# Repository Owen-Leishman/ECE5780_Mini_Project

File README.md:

# Demonstration Neural Interface
>[!warning]
>This is a demonstration device, this hardware is relatively untested and not gauranteed to be safe! This is not designed live test subjects!

## Overview
This is a demonstration neural interface which is meant to explore how neural interfaces work.  This device can measure four differential signals at a time which can be used to measure nerve impulses and are tolerant of ±9V. It also has a current mode stimulation channel which can create ±1mA signals with 9 bits of resolution as a means to give feedback to the nerves. The stimulation channel can handle electrodes with up to 9kΩ. The device also has a temperature sensor to measure how much it heats up to ensure that it would be safe if implanted (at least temperature wise). The device can be controlled over wifi, and is fully battery powered.

(A logo was edited out on the bottom left corner of the device, the photo is otherwise not edited)

## Organization
- [Firmware](/Firmware/Neural_Demo/) contains the code that the device runs.
- [Hardware](/Hardware/) contains the design of the device.
- [Software](/Software/) contains the code used to interface with the device.

For information on how to use the device refer to the [software directory](/Software/).

For information on how to manufacture the device refer to the [hardware directory](/Hardware/).

## Results
The device has exceptional accuracy and can measure down to the uV using its discreate ADC.

This test was run using an external signal generator to create a 1mV peak-to-peak sine wave at 500mHz. (This test was also done with old software and firmware some of the ADC configuration has been changed).

The demonstration software makes it possible to measure all four channels in real time over wifi, and the measured stimulation current. The software also makes it possible to control the amplitude and waveform the current stimulation uses.

The discreate ADC broke so the ESP32's onboard ADC (which is much worse) was used for this test. An external signal generator was connected to channel 1 to create a 1V peak-to-peak sine wave, and an external load resistor was used to connect the stimulation output to ground.

# Design Overview
Here are is the top level design of the device, for detailed information on the desing refer to the [hardware directory](Hardware).

## Top Level Design

The ESP32 microcontroller is used to control the whole device. The analog frontend is used to aquire data from the differential inputs, and output stimulation signals. The power distrobution block manages the battery and all of the supply voltages.

## Analog Frontend

## Power Distrobution

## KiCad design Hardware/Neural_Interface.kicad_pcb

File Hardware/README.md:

# Demonstration Neural Interface Hardware
>[!warning]
>This is a demonstration device, this hardware is relatively untested and not gauranteed to be safe! This is not designed live test subjects!

>[!note]
>Made with KiCad version 7.0,  [Kicad Download](https://www.kicad.org/download/)

The hardware for the demonstration neural interface.

## Tasks
- [ ] Test BQ51013BRHLR wirless power IC.
- [ ] Add voltage divider/modify signal path for onboard ADC.
- [ ] Find replacement for AD8067ARTZ operational amplifier used in the current source.
- [ ] Find issues with MCP3464 ADC (may have been ESD)

# Assembled Device

>[!warning]
>This device uses BGA components and is not trivial to solder. Due to the large amount of surface mount components on the device it is recomended to use a stencil and a reflow oven for soldering.

## Current Source Fix

The AD8067ARTZ was broken (reason still unknown) so a LF353N was used to replace it for testing.

## Onboard ADC Fix

The MCP3464RT ADC broke so the ESP32's onboard ADC was used. The onboard ADC can not measure voltages larger than ~200mV so voltage dividers were added to divide all of the signals into that range, 4.7K and 180R resistors were used to create the voltage dividers. This creates a lot of noise and distortion in the signals. Due to this onboard ADC will not be used or supported in future revisions.

# Schematics
## Top Level Schematic

Schematic for the ESP32 S2-mini and supporting circuitry which is used to control the device. Jumpers are added between the ESP32's gpio and board signals to make it possible to rerout signals if there is a conflict, or prevent interference for analog signals if the onboard ADC is not being used. The temperature sensor is also on this schematic.

## Analog Frontend Schematic

Schematic for the analog frontend used to measure "neural" signals and output current mode stimulation. The differential input signals are fed into voltage dividers to ensure that the maximum voltage that reaches the system is ±3.3V, and to create a 1MΩ input impedance. Instrumentation amplifiers are used to amplify the differential signals (satureates at ±1V but is tolerant fo ±9V) and convert them to single ended signals (0-3.3V) centered around Vref (1.6V). The outut of the instrumentation amplifiers is fed into a buffered opamp with a shotkey diode to prevent negative voltages from reaching the ADC when the instrumentation amplifiers get saturated with a negative signal (Ie. an input of -9V), this opamp will likely be removed in future revisions. Low pass filterers and decoupling capacitors are implemented throughout the design to reduce noise.

The current mode stimulation is created using an advanced howland current source implementation based on an [article by Nick Jiang from Analog Devices](https://www.analog.com/en/resources/analog-dialogue/articles/a-large-current-source-with-high-accuracy-and-fast-settling.html). The current sources is controlled by using both DACs on the ESP32, one DAC is used for creating positive currents while the other is used to create negative curents. The maximum output current is ±1mA when 3.3V is supplied by one of the DACs. The maximum probe impedance the current source can handle is 9kΩ, since the stimulation voltage is ±9V. A capacitor is added in series to the output current to prevent continous stimulation in case of a device malfunction (this capacitor was shorted to test the current source at low frequencies).

## Power Manegement Schematic

Schematic for the power manegement circuitry which supplies power to the device and maneges the battery. The device can be powered from using wireless charging, USB type C, or the onboard battery. The BQ51013BRHLR wireless charging IC automatically selects if the BQ25185DLHR battery charging IC will be suplied with usb power or wireless power based on which one is present. The battery charging IC controlls the battery charge rate, and charge and discharge threshold and determines if the voltage regulators for the rest of the system will be supplied with battery power or the power selected by the wireless charging IC. A BQ27427YZFR is placed in series with the battery to measure battery life.

There are three voltage regulators on the device. A buck converter supplies Vsys (+3.3V) to power the ESP32 and TMP117, it is always on when voltage is present. A differential boost converter suplies Vstim (±9V) which poweres the constant current source and is controlled by the ESP32. The rest of the analog frontend is powered with a differential linear dropout regulator (LDO) which is powered from Vstim and reduces the supply noise caused by the switching regulators creating ±3.3V, this is not very effecient and will likely be changed in future revisions. The LDO is always on whenever Vstim is present.

# PCB Layout

>[!note]
>These figures are for reference, there may be some visual issues due to how KiCad exports SVG files.

## Top PCB Layout

## Bottom PCB Layout

## 3D Render

# Ordering
The design is layed out as a two layer board following [JLC PCB's](https://jlcpcb.com/) constraints, and all components are placed on the top layer. To order zip the [NSD_V1-0](Hardware/NSD_V1-0) directory and submit it to JLC PCB. A stencil can also be ordered from JLC PCB.

All of the parts other than the battery and battery connector can be ordered from [Mouser Electronics](https://www.mouser.com/) and listed [here](Hardware/MouserPartsOrder.xls). The battery and battery connector can be ordered from [DigiKey](https://www.digikey.com/) and are listed [here](Hardware/DigiKeyPartsOrder.xlsx). The [BOM](Hardware/BOM.csv) does not reference passive parts with manufacturer names. Additionaly 2.54mm headers are not included in either of these lists.

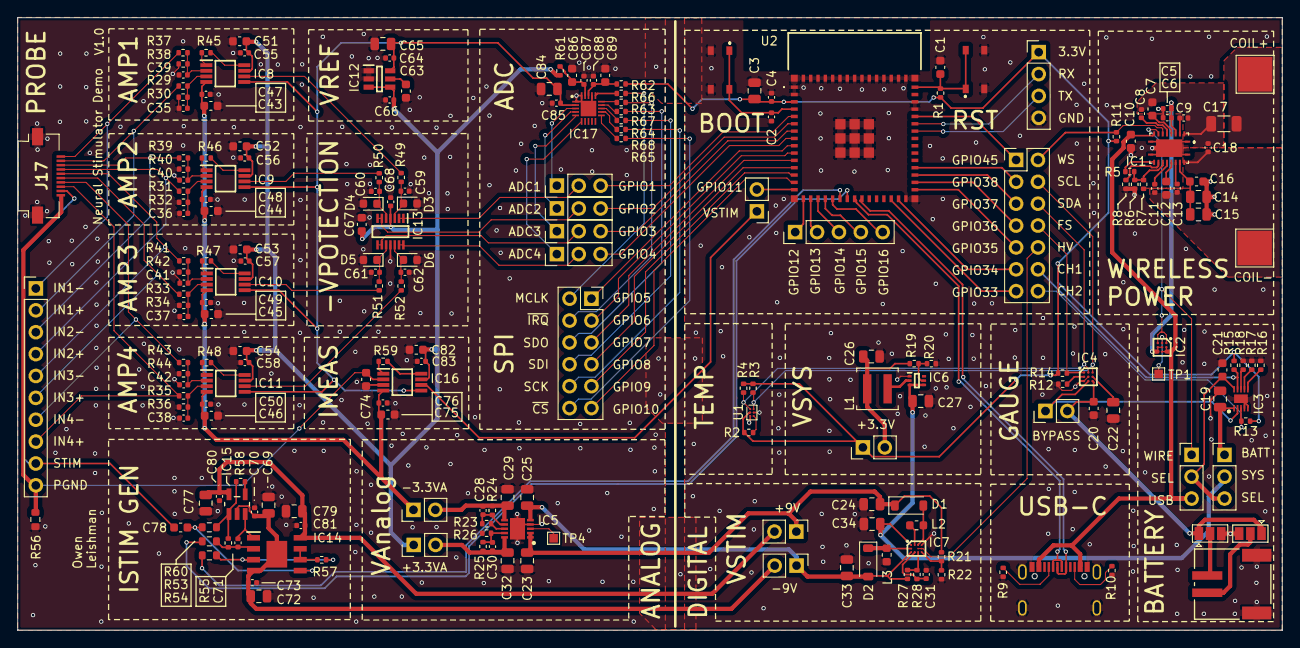
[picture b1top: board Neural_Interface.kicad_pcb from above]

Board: 2 copper layers, 146.9 x 71.1 mm, 214 parts (0 on the bottom side), 161 nets.

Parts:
C1, C10, C16, C20, C21, C43, C44, C45, C46, C51, C52, C53, C54, C63, C67, C74, C75, C78, C82, C86, C89: 1u; C_0603_1608Metric
C2, C4, C5, C31, C47, C48, C49, C50, C55, C56, C57, C58, C64, C66, C68, C70, C73, C76, C80, C81, C83, C85, C87, C88: 100n; C_0402_1005Metric
C3, C14, C15, C19, C22, C23, C24, C25, C26, C27, C29, C32, C33, C34, C65, C69, C72, C77, C79, C84: 10u; C_0805_2012Metric
C6, C9, C13, C28, C30: 10n; C_0402_1005Metric
C7, C12: 470n; C_0603_1608Metric
C8, C11: 47n; C_0402_1005Metric
C17: 82n; C_1206_3216Metric
C18: 820p; C_0402_1005Metric
C35, C36, C37, C38, C39, C40, C41, C42, C59, C60, C61, C62: 30p; C_0402_1005Metric
C71: 200p; C_0402_1005Metric
D1, D2: MBR130T1G; D_SOD-123
D3, D4, D5, D6: CDBU0130L-HF; D_0603_1608Metric
IC1: BQ51013BRHLR; BQ51050BRHLR
IC2: CSD75207W15; BGA9C50P3X3_146X146X62
IC3: BQ25185DLHR; SON40P220X200X80-11N
IC4: BQ27427YZFR; BGA9C50P3X3_158X162X62
IC5: TPS7A3901DSCR; SON50P300X300X80-11N-D
IC6: TLV62585DRLR; SOTFL50P160X60-6N
IC7: BD8316GWL-E2; BGA11C40P4X3_180X150X55
IC8, IC9, IC10, IC11, IC16: INA823DGKR; SOP65P490X110-8N
IC12: REF35160QDBVR; SOT95P280X145-6N
IC13: LM324LVIDYYR; SOP50P326X110-14N
IC14: ADA4898-2YRDZ; SOIC127P600X175-9N
IC15: AD8067ARTZ-REEL7; SOT95P280X145-5N
IC17: MCP3464RT-E_NC; QFN40P300X300X60-21N-D
J1: Conn_02x07_Odd_Even; PinHeader_2x07_P2.54mm_Vertical
J2: Conn_02x06_Odd_Even; PinSocket_2x06_P2.54mm_Vertical
J3: Conn_01x05; PinHeader_1x05_P2.54mm_Vertical
J4: Conn_01x04; PinHeader_1x04_P2.54mm_Vertical
J5, J10, J18, J19, J20, J21: Conn_01x03; PinHeader_1x03_P2.54mm_Vertical
J6, J11, J12, J13, J14, J15, J22: Conn_01x02; PinHeader_1x02_P2.54mm_Vertical
J7: S2B-PH-SM4-TB; CONN_S2B-PH-SM4-TB_JST
J8, J9: Conn_01x03; SolderJumper-3_P1.3mm_Open_Pad1.0x1.5mm
J16: Conn_01x10; PinHeader_1x10_P2.54mm_Vertical
J17: 505110-1092; 5051101092
L1: 1uH; L_Coilcraft_XAL4020-XXX
L2, L3: 4.7uH; L_0603_1608Metric
R1, R2, R3, R4, R8, R11, R12, R13, R14, R15, R16, R22, R23, R26, R28, R49, R50, R51, R52: 10k; R_0402_1005Metric
R5: 330; R_0402_1005Metric
R6: 196; R_0402_1005Metric
R7: 20k; R_0402_1005Metric
R9, R10: 5.1k; R_0402_1005Metric
R17: 130k; R_0402_1005Metric
R18: 3k; R_0402_1005Metric
R19: 453k; R_0402_1005Metric
R20, R21: 100k; R_0402_1005Metric
R24: 28k; R_0402_1005Metric
R25: 17.8k; R_0402_1005Metric
R27: 90.9k; R_0402_1005Metric
R29, R31, R33, R35, R37, R39, R41, R43: 600k; R_0402_1005Metric
R30, R32, R34, R36, R38, R40, R42, R44: 332k; R_0402_1005Metric
R45, R46, R47, R48: 24.9k; R_0402_1005Metric
R53, R54: 82.5k; R_0603_1608Metric
R55, R57: 100R; R_0402_1005Metric
R56: 1R; R_0603_1608Metric
R58: 2k; R_0402_1005Metric
R59: 200; R_0402_1005Metric
R60: 4R; R_0603_1608Metric
R61, R62, R63, R64, R65, R66, R67, R68: 10R; R_0402_1005Metric
SW1: RESET; PTS815SJM250SMTRLFS
SW2: BOOT; PTS815SJM250SMTRLFS
TP1, TP4: TestPoint; TestPoint_Pad_1.0x1.0mm
TP2, TP3: TestPoint; TestPoint_Pad_4.0x4.0mm
U1: TMP117; Texas_DSBGA-6_0.95x1.488mm_Layout2x3_P0.4mm
U2: ESP32S2MINI1N4R2
U3: USB4105

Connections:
5v_Batt: C19.1, IC3.1 (SYS), J10.1
5v_Sel: C21.1, IC3.10 (IN), J5.2, J10.3
5v_Sys: C27.1, C34.1, IC6.3 (VIN), IC6.4 (EN), IC7.A1 (VDD), J10.2
5v_USB: C10.1, IC1.9 (AD), IC2.A2 (D1_1), IC2.A3 (D1_2), IC2.B3 (D1_3), J5.3, U3.2 (A4-B9), U3.11 (B4-A9)
5v_Wireless: C5.1, C6.1, IC1.4 (OUT), IC2.B2 (D2_1), IC2.C2 (D2_2), IC2.C3 (D2_3)
+3.3V: C3.1, C4.1, J4.1, J13.1, R1.1, R2.2, R3.2, R4.2, R11.1, R13.1, R14.1, R15.1, R62.2, U1.B1 (V+), U2.3 (3V3)
+3.3VA: C51.1, C52.1, C53.1, C54.1, C55.1, C56.1, C57.1, C58.1, C66.1, C67.1, C68.1, C82.1, C83.1, IC8.7 (+VS), IC9.7 (+VS), IC10.7 (+VS), IC11.7 (+VS), IC12.3 (EN), IC12.4 (VIN), IC13.4 (V+), IC16.7 (+VS), J14.1, R61.2
+3.3va: C30.1, C32.1, IC5.10 (OUTP), J14.2, R25.1
+3v: C26.1, J13.2, L1.1, R19.1
+9v: C23.1, C24.1, D1.1 (K), IC5.1 (INP), IC5.2 (EN), J11.1, R21.1
-3.3va: C28.2, C29.1, IC5.6 (OUTN), J15.2, R24.2
-3V3: C43.1, C44.1, C45.1, C46.1, C47.1, C48.1, C49.1, C50.1, C75.1, C76.1, IC8.4 (-VS), IC9.4 (-VS), IC10.4 (-VS), IC11.4 (-VS), IC16.4 (-VS), J15.1
-9v: C25.1, C33.1, D2.2 (A), IC5.5 (INN), IC7.C1 (DIS1), J12.1, R27.1
AC1: C7.1, C8.1, C9.2, C17.2, C18.1, IC1.2 (AC1)
AC2: C11.1, C12.1, C13.2, C18.2, IC1.19 (AC2), TP3.1
ADC_1: J19.3, U2.5 (IO1)
ADC_2: J18.3, U2.6 (IO2)
ADC_3: J20.3, U2.7 (IO3)
ADC_4: J21.3, U2.8 (IO4)
ADC_5: J22.2, U2.15 (IO11)
ALERT: R2.1, U1.C2 (ALERT)
BOOT: C2.2, SW2.1, U2.4 (IO0)
Batt+: J7.1, J8.2
Batt-: J7.2, J9.2
CHRG_STAT1: IC3.9 (STAT1), J1.12, R15.2
CHRG_STAT2: IC3.3 (STAT2), J1.14, R13.2
COIL+: C17.1, TP2.1
D+: U2.24 (IO20), U3.6 (A6), U3.8 (B6)
D-: U2.23 (IO19), U3.5 (B7), U3.7 (A7)
Fuel_Status: IC4.A1 (GPOUT), J1.8, R14.2
GND: C1.2, C2.1, C3.2, C4.2, C5.2, C6.2, C10.2, C14.2, C15.2, C16.2, C19.2, C20.2, C21.2, C22.2, C23.2, C24.2, C25.2, C26.2, C27.2, C29.2, C31.2, C32.2, C33.2, C34.2, C35.2, C36.2, C37.2, C38.2, C39.2, C40.2, C41.2, C42.2, C43.2, C44.2, C45.2, C46.2, C47.2, C48.2, C49.2, C50.2, C51.2, C52.2, C53.2, C54.2, C55.2, C56.2, C57.2, C58.2, C59.2, C60.2, C61.2, C62.2, C63.2, C64.2, C65.2, C66.2, C67.2, C68.2, C69.2, C70.2, C72.2, C73.2, C74.2, C75.2, C76.2, C77.2, C79.2, C80.2, C81.2, C82.2, C83.2, C84.2, C85.2, C86.2, C87.2, C88.2, C89.2, D3.2 (A), D4.2 (A), D5.2 (A), D6.2 (A), IC1.1 (PGND_1), IC1.10 (EN1), IC1.11 (EN2), IC1.20 (PGND_2), IC1.21 (EP), IC3.4 (~CE), IC3.5 (GND), IC3.11 (EP), IC4.B2 (VSS_1), IC4.C1 (VSS_2), IC5.4 (GND), IC5.11 (EP), IC6.1 (GND), IC7.A4 (GND), IC12.1 (GND_1), IC12.2 (GND_2), IC13.11 (V-), IC16.3 (+IN), IC17.1 (REFIN-), IC17.17 (DGND), IC17.20 (AGND), IC17.21 (EP), J4.4, J7.3 (SHIELD), J7.4 (SHIELD), J8.3, J9.3, J17.11, J17.12, L3.2, R6.2, R8.2, R9.1, R10.2, R12.2, R16.2, R17.2, R18.2, R20.2, R22.2, R26.2, R30.1, R32.1, R34.1, R36.1, R38.1, R40.1, R42.1, R44.1, R56.1, SW1.2, SW2.2, U1.B2 (GND), U1.C1 (ADD0), U2.1 (GND), U2.2 (GND), U2.30 (GND), U2.42 (GND), U2.43 (GND), U2.46 (GND), U2.47 (GND), U2.48 (GND), U2.49 (GND), U2.50 (GND), U2.51 (GND), U2.52 (GND), U2.53 (GND), U2.54 (GND), U2.55 (GND), U2.56 (GND), U2.57 (GND), U2.58 (GND), U2.59 (GND), U2.60 (GND), U2.61 (GND), U2.62 (GND), U2.63 (GND), U2.64 (GND), U2.65 (GND), U2.66, U2.67, U2.68, U2.69, U2.70, U2.71, U2.72, U2.73, U3.1 (A1-B12), U3.12 (B1-A12), U3.13 (GND)
GPIO5: J2.1, U2.9 (IO5)
GPIO6: J2.3, U2.10 (IO6)
GPIO7: J2.5, U2.11 (IO7)
GPIO8: J2.7, U2.12 (IO8)
GPIO9: J2.9, U2.13 (IO9)
GPIO10: J2.11, U2.14 (IO10)
GPIO12: J3.1, U2.16 (IO12)
GPIO13: J3.2, U2.17 (IO13)
GPIO14: J3.3, U2.18 (IO14)
GPIO15: J3.4, U2.19 (IO15)
GPIO16: J3.5, U2.20 (IO16)
GPIO33: J1.13, U2.28 (IO33)
GPIO34: J1.11, U2.29 (IO34)
GPIO35: J1.9, U2.31 (IO35)
GPIO36: J1.7, U2.32 (IO36)
GPIO37: J1.5, U2.33 (IO37)
GPIO38: J1.3, U2.34 (IO38)
GPIO45: J1.1, U2.41 (IO45)
HV_En: IC7.B3 (STB1), IC7.B4 (STB2), J1.10
Istim: IC16.6 (OUT), J22.1
MCLK: J2.2, R66.1
unnamed: D1.2 (A), IC7.A3 (LX2), L2.1
unnamed: D2.1 (K), IC7.B1 (LX1), L3.1
unnamed: C59.1, D3.1 (K), IC13.3 (IN1+), R49.1
unnamed: C60.1, D4.1 (K), IC13.5 (IN2+), R50.1
unnamed: C61.1, D5.1 (K), IC13.10 (IN3+), R51.1
unnamed: C62.1, D6.1 (K), IC13.12 (IN4+), R52.1
unnamed: C9.1, IC1.3 (BOOT1)
unnamed: C13.1, IC1.17 (BOOT2)
unnamed: C7.2, IC1.5 (CLAMP1)
unnamed: C12.2, IC1.16 (CLAMP2)
unnamed: C8.2, IC1.6 (COMM1)
unnamed: C11.2, IC1.15 (COMM2)
unnamed: IC1.14 (FOD), R5.2, R6.1, R7.1
unnamed: IC1.12 (ILIM), R5.1
unnamed: IC1.13 (TS/CTRL), R8.1
unnamed: IC2.B1 (SS), TP1.1
unnamed: IC3.7 (ILIM/VSET), R17.1
unnamed: IC3.8 (ISET), R18.1
unnamed: IC3.6 (TS/MR), R16.1
unnamed: IC4.B1 (BIN), R12.1
unnamed: C22.1, IC4.B3 (VDD)
unnamed: IC5.8 (BUF), R23.1
unnamed: C28.1, IC5.7 (FBN), R23.2, R24.1
unnamed: C30.2, IC5.9 (FBP), R25.2, R26.1
unnamed: IC5.3 (NR/SS), TP4.1
unnamed: IC6.5 (FB), R19.2, R20.1
unnamed: IC6.2 (SW), L1.2
unnamed: IC7.A2 (HS2L), L2.2
unnamed: IC7.C4 (INV2), R21.2, R22.1
unnamed: IC7.C3 (NON1), R27.2, R28.1
unnamed: C31.1, IC7.C2 (VREF), R28.2
unnamed: C35.1, IC8.3 (+IN), R29.1, R30.2
unnamed: C39.1, IC8.2 (-IN), R37.1, R38.2
unnamed: IC8.1 (RG_1), R45.2
unnamed: IC8.8 (RG_2), R45.1
unnamed: C36.1, IC9.3 (+IN), R31.1, R32.2
unnamed: C40.1, IC9.2 (-IN), R39.1, R40.2
unnamed: IC9.1 (RG_1), R46.2
unnamed: IC9.8 (RG_2), R46.1
unnamed: C37.1, IC10.3 (+IN), R33.1, R34.2
unnamed: C41.1, IC10.2 (-IN), R41.1, R42.2
unnamed: IC10.1 (RG_1), R47.2
unnamed: IC10.8 (RG_2), R47.1
unnamed: C38.1, IC11.3 (+IN), R35.1, R36.2
unnamed: C42.1, IC11.2 (-IN), R43.1, R44.2
unnamed: IC11.1 (RG_1), R48.2
unnamed: IC11.8 (RG_2), R48.1
unnamed: C63.1, IC12.5 (NR)
unnamed: IC14.3 (+IN1), R54.2, R57.1
unnamed: C78.2, IC14.5 (+IN2), R60.2
unnamed: C71.1, IC14.2 (-IN1), R53.2, R55.1
unnamed: IC14.6 (-IN2), IC14.7 (VOUT2), R57.2
unnamed: C71.2, IC14.1 (VOUT1), IC15.3 (+IN)
unnamed: IC15.4 (-IN), R58.2
unnamed: IC15.1 (VOUT), R55.2, R58.1, R60.1
unnamed: IC16.1 (RG_1), R59.2
unnamed: IC16.8 (RG_2), R59.1
unnamed: C86.1, C87.1, IC17.19 (AVDD), R61.1
unnamed: C88.1, C89.1, IC17.18 (DVDD), R62.1
unnamed: IC17.16 (MCLK), R66.2
unnamed: IC17.12 (SCK), R68.2
unnamed: IC17.13 (SDI), R64.2
unnamed: IC17.14 (SDO), R67.2
unnamed: IC17.11 (~CS), R65.2
unnamed: IC17.15 (~IRQ/MDAT), R63.2
unnamed: R9.2, U3.4 (A5)
unnamed: R10.1, U3.10 (B5)
OADC_1: IC17.3 (CH0), J19.1
OADC_2: IC17.4 (CH1), J18.1
OADC_3: IC17.5 (CH2), J20.1
OADC_4: IC17.6 (CH3), J21.1
OUT_SEL: IC1.8 (~AD-EN), IC2.A1 (G1), IC2.C1 (G2), J5.1
P_1: IC13.1 (OUT1), IC13.2 (IN1-), J19.2
P_2: IC13.6 (IN2-), IC13.7 (OUT2), J18.2
P_3: IC13.8 (OUT3), IC13.9 (IN3-), J20.2
P_4: IC13.13 (IN4-), IC13.14 (OUT4), J21.2
Probe_1: IC8.6 (OUT), R49.2
Probe_2: IC9.6 (OUT), R50.2
Probe_3: IC10.6 (OUT), R51.2
Probe_4: IC11.6 (OUT), R52.2
Probe_in_1+: J16.2, J17.2, R29.2
Probe_in_1-: J16.1, J17.1, R37.2
Probe_in_2+: J16.4, J17.4, R31.2
Probe_in_2-: J16.3, J17.3, R39.2
Probe_in_3+: J16.6, J17.6, R33.2
Probe_in_3-: J16.5, J17.5, R41.2
Probe_in_4+: J16.8, J17.8, R35.2
Probe_in_4-: J16.7, J17.7, R43.2
RECT: C14.1, C15.1, C16.1, IC1.18 (RECT), R7.2
RESET: C1.1, R1.2, SW1.1, U2.45 (EN)
RX: J4.2, U2.40 (RXD0)
SCK: J2.10, R68.1
SCL: IC4.A3 (SCL), J1.4, R3.1, U1.A2 (SCL)
SDA: IC4.A2 (SDA), J1.6, R4.1, U1.A1 (SDA)
SDI: J2.8, R64.1
SDO: J2.6, R67.1
Stim+: C77.1, C79.1, C80.1, C81.1, IC14.8 (+VS), IC15.5 (+VS), J11.2
Stim-: C69.1, C70.1, C72.1, C73.1, IC14.4 (-VS), IC14.9 (EP), IC15.2 (-VS), J12.2
Stim_control+: R53.1, U2.22 (IO18)
Stim_control-: R54.1, U2.21 (IO17)
Stim_gnd: C74.1, IC16.2 (-IN), J16.10, J17.10, R56.2
Stim_out: C78.1, J16.9, J17.9
TX: J4.3, U2.39 (TXD0)
V_Batt: C20.1, IC4.C3 (BAT), J6.2, J8.1, J9.1
V_Fuel: IC3.2 (BAT), IC4.C2 (SRX), J6.1
Vref: C64.1, C65.1, C84.1, C85.1, IC8.5 (REF), IC9.5 (REF), IC10.5 (REF), IC11.5 (REF), IC12.6 (VREF), IC16.5 (REF), IC17.2 (REFIN+/OUT)
Wireless_Status: IC1.7 (~CHG), J1.2, R11.2
~CS: J2.12, R65.1
~IRQ: J2.4, R63.1

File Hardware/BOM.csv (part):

"Item","Qty","Reference(s)","Value","LibPart","Footprint","Datasheet","DNP","Height","Manufacturer_Name","Manufacturer_Part_Number","Mouser Part Number","Mouser Price/Stock"
"1","21","C1, C10, C16, C20, C21, C43, C44, C45, C46, C51, C52, C53, C54, C63, C67, C74, C75, C78, C82, C86, C89","1u","Device:C","Capacitor_SMD:C_0603_1608Metric","~","","","","","",""
"2","24","C2, C4, C5, C31, C47, C48, C49, C50, C55, C56, C57, C58, C64, C66, C68, C70, C73, C76, C80, C81, C83, C85, C87, C88","100n","Device:C","Capacitor_SMD:C_0402_1005Metric","~","","","","","",""
"3","20","C3, C14, C15, C19, C22, C23, C24, C25, C26, C27, C29, C32, C33, C34, C65, C69, C72, C77, C79, C84","10u","Device:C","Capacitor_SMD:C_0805_2012Metric","~","","","","","",""
"4","5","C6, C9, C13, C28, C30","10n","Device:C","Capacitor_SMD:C_0402_1005Metric","~","","","","","",""
"5","2","C7, C12","470n","Device:C","Capacitor_SMD:C_0603_1608Metric","~","","","","","",""
"6","2","C8, C11","47n","Device:C","Capacitor_SMD:C_0402_1005Metric","~","","","","","",""
"7","1","C17","82n","Device:C","Capacitor_SMD:C_1206_3216Metric","~","","","","","",""
"8","1","C18","820p","Device:C","Capacitor_SMD:C_0402_1005Metric","~","","","","","",""
"9","12","C35, C36, C37, C38, C39, C40, C41, C42, C59, C60, C61, C62","30p","Device:C","Capacitor_SMD:C_0402_1005Metric","~","","","","","",""
"10","1","C71","200p","Device:C","Capacitor_SMD:C_0402_1005Metric","~","","","","","",""
"11","2","D1, D2","MBR130T1G","Device:D_Schottky","Diode_SMD:D_SOD-123","https://www.mouser.com/datasheet/2/308/1/MBR130T1_D-2315168.pdf","","","","","",""
"12","4","D3, D4, D5, D6","CDBU0130L-HF","Device:D_Schottky","Diode_SMD:D_0603_1608Metric","https://www.mouser.com/datasheet/2/308/1/MBR130T1_D-2315168.pdf","","","","","",""
"13","1","IC1","BQ51013BRHLR","Neural_Components:BQ51013BRHLR","Neural_Footprints:BQ51050BRHLR","http://www.ti.com/lit/ds/symlink/bq51013b.pdf","","","Texas Instruments","BQ51013BRHLR","595-BQ51013BRHLR","https://www.mouser.co.uk/ProductDetail/Texas-Instruments/BQ5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"
"14","1","IC2","CSD75207W15","Neural_Components:CSD75207W15","Neural_Footprints:BGA9C50P3X3_146X146X62","","","0.62","Texas Instruments","CSD75207W15","595-CSD75207W15","https://www.mouser.co.uk/ProductDetail/Texas-Instruments/CSD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"
"15","1","IC3","BQ25185DLHR","Neural_Components:BQ25185DLHR","Neural_Footprints:SON40P220X200X80-11N","https://www.ti.com/lit/ds/symlink/bq25185.pdf?ts=17068575613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","","0.8","Texas Instruments","BQ25185DLHR","595-BQ25185DLHR","https://www.mouser.co.uk/ProductDetail/Texas-Instruments/BQ2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"
"16","1","IC4","BQ27427YZFR","Neural_Components:BQ27427YZFR","Neural_Footprints:BGA9C50P3X3_158X162X62","https://www.ti.com/lit/ds/symlink/bq27427.pdf?ts=16876982679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","","0.625","Texas Instruments","BQ27427YZFR","595-BQ27427YZFR","https://www.mouser.co.uk/ProductDetail/Texas-Instruments/BQ2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"
"17","1","IC5","TPS7A3901DSCR","Neural_Components:TPS7A3901DSCR","Neural_Footprints:SON50P300X300X80-11N-D","http://www.ti.com/lit/gpn/tps7a39","","0.8","Texas Instruments","TPS7A3901DSCR","595-TPS7A3901DSCR","https://www.mouser.co.uk/ProductDetail/Texas-Instruments/TPS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"
"18","1","IC6","TLV62585DRLR","Neural_Components:TLV62585DRLR","Neural_Footprints:SOTFL50P160X60-6N","http://www.ti.com/lit/gpn/tlv62585","","0.6","Texas Instruments","TLV62585DRLR","595-TLV62585DRLR","https://www.mouser.co.uk/ProductDetail/Texas-Instruments/TLV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"
"19","1","IC7","BD8316GWL-E2","Neural_Components:BD8316GWL-E2","Neural_Footprints:BGA11C40P4X3_180X150X55","https://fscdn.rohm.com/en/products/databook/datasheet/ic/pow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","","0.55","ROHM Semiconductor","BD8316GWL-E2","755-BD8316GWL-E2","https://www.mouser.co.uk/ProductDetail/ROHM-Semiconductor/BD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"
"20","5","IC8, IC9, IC10, IC11, IC16","INA823DGKR","Neural_Components:INA823DGKR","Neural_Footprints:SOP65P490X110-8N","https://www.ti.com/lit/ds/symlink/ina823.pdf?ts=171040527465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","","1.1","Texas Instruments","INA823DGKR","595-INA823DGKR","https://www.mouser.co.uk/ProductDetail/Texas-Instruments/INA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"
"21","1","IC12","REF35160QDBVR","Neural_Components:REF35160QDBVR","Neural_Footprints:SOT95P280X145-6N","https://www.ti.com/lit/ds/symlink/ref35.pdf?ts=1675771464754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","","1.45","Texas Instruments","REF35160QDBVR","595-REF35160QDBVR","https://www.mouser.co.uk/ProductDetail/Texas-Instruments/REF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"
"22","1","IC13","LM324LVIDYYR","Neural_Components:LM324LVIDYYR","Neural_Footprints:SOP50P326X110-14N","https://www.ti.com/lit/ds/symlink/lm358lv.pdf?HQS=dis-mous-n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","","1.1","Texas Instruments","LM324LVIDYYR","595-LM324LVIDYYR","https://www.mouser.co.uk/ProductDetail/Texas-Instruments/LM3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"
"23","1","IC14","ADA4898-2YRDZ","Neural_Components:ADA4898-2YRDZ","Neural_Footprints:SOIC127P600X175-9N","https://www.analog.com/media/en/technical-documentation/data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","","1.75","Analog Devices","ADA4898-2YRDZ","584-ADA4898-2YRDZ","https://www.mouser.co.uk/ProductDetail/Analog-Devices/ADA489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"
"24","1","IC15","AD8067ARTZ-REEL7","Neural_Components:AD8067ARTZ-REEL7","Neural_Footprints:SOT95P280X145-5N","","","","Analog Devices","AD8067ARTZ-REEL7","584-AD8067ARTZ-R7","https://www.mouser.co.uk/ProductDetail/Analog-Devices/AD8067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"
"25","1","IC17","MCP3464RT-E_NC","Neural_Components:MCP3464RT-E_NC","Neural_Footprints:QFN40P300X300X60-21N-D","https://componentsearchengine.com/Datasheets/2/MCP3464RT-E_NC.pdf","","0.6","Microchip","MCP3464RT-E/NC","579-MCP3464RT-E/NC","https://www.mouser.co.uk/ProductDetail/Microchip-Technology/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"
"26","1","J1","Conn_02x07_Odd_Even","Connector_Generic:Conn_02x07_Odd_Even","Connector_PinHeader_2.54mm:PinHeader_2x07_P2.54mm_Vertical","~","","","","","",""
"27","1","J2","Conn_02x06_Odd_Even","Connector_Generic:Conn_02x06_Odd_Even","Connector_PinSocket_2.54mm:PinSocket_2x06_P2.54mm_Vertical","~","","","","","",""
"28","1","J3","Conn_01x05","Connector_Generic:Conn_01x05","Connector_PinHeader_2.54mm:PinHeader_1x05_P2.54mm_Vertical","~","","","","","",""
"29","1","J4","Conn_01x04","Connector_Generic:Conn_01x04","Connector_PinHeader_2.54mm:PinHeader_1x04_P2.54mm_Vertical","~","","","","","",""
"30","6","J5, J10, J18, J19, J20, J21","Conn_01x03","Connector_Generic:Conn_01x03","Connector_PinHeader_2.54mm:PinHeader_1x03_P2.54mm_Vertical","~","","","","","",""
"31","7","J6, J11, J12, J13, J14, J15, J22","Conn_01x02","Connector_Generic:Conn_01x02","Connector_PinHeader_2.54mm:PinHeader_1x02_P2.54mm_Vertical","~","","","","","",""
"32","1","J7","S2B-PH-SM4-TB","Neural_Components:S2B-PH-SM4-TB","Neural_Footprints:CONN_S2B-PH-SM4-TB_JST","S2B-PH-SM4-TB","","","","","",""
"33","2","J8, J9","Conn_01x03","Connector_Generic:Conn_01x03","Jumper:SolderJumper-3_P1.3mm_Open_Pad1.0x1.5mm","~","","","","","",""
"34","1","J16","Conn_01x10","Connector_Generic:Conn_01x10","Connector_PinHeader_2.54mm:PinHeader_1x10_P2.54mm_Vertical","~","","","","","",""
"35","1","J17","505110-1092","Neural_Components:505110-1092","Neural_Footprints:5051101092","https://www.molex.com/webdocs/datasheets/pdf/en-us/505110109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","","0","Molex","505110-1092","538-505110-1092","https://www.mouser.co.uk/ProductDetail/Molex/505110-1092?qs=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"
"36","1","L1","1uH","Device:L","Inductor_SMD:L_Coilcraft_XAL4020-XXX","https://www.mouser.com/ProductDetail/Coilcraft/XFL4020-102ME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","","","","","",""
"37","2","L2, L3","4.7uH","Device:L","Inductor_SMD:L_0603_1608Metric","https://www.mouser.com/datasheet/2/281/1/JELF243B_0033-1634182.pdf","","","","","",""
"38","19","R1, R2, R3, R4, R8, R11, R12, R13, R14, R15, R16, R22, R23, R26, R28, R49, R50, R51, R52","10k","Device:R","Resistor_SMD:R_0402_1005Metric","~","","","","","",""
"39","1","R5","330","Device:R","Resistor_SMD:R_0402_1005Metric","~","","","","","",""
"40","1","R6","196","Device:R","Resistor_SMD:R_0402_1005Metric","~","","","","","",""
"41","1","R7","20k","Device:R","Resistor_SMD:R_0402_1005Metric","~","","","","","",""
"42","2","R9, R10","5.1k","Device:R","Resistor_SMD:R_0402_1005Metric","~","","","","","",""
"43","1","R17","130k","Device:R","Resistor_SMD:R_0402_1005Metric","~","","","","","",""
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
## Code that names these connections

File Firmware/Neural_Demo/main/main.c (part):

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
//****************Pin Definitions*******************

#define ADC_1   1
#define ADC_2   2
#define ADC_3   3
#define ADC_4   4
#define ADC_5   11

#define STIM_P  17
#define STIM_N  18

#define WIRELESS_STATUS 45
#define FUEL_STATUS     36
#define HIGH_VOLTAGE_EN 35
#define CHARGE_STAT_1   34
#define CHARGE_STAT_2   33
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
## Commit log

2024-03-21 Create .gitignore
    Ignore illustrator files used to create figures
2024-03-21 Add figures
2024-03-21 Add background to figures
2024-03-21 Add ESP32 to design
2024-03-21 Reorganize files
2024-03-25 Add charging circuitry
    Warning Voltage dividers for switching regulator not speced correctly!!
2024-03-26 Power Management Complete
2024-03-27 Design Analog Frontend
2024-03-27 Add Current Measurement
2024-03-29 Spec all components
2024-04-01 Start Layout
2024-04-02 Completed Layout
2024-04-03 Create ESP project
2024-04-03 Fix include error
2024-04-04 Add code to read temperature sensor
    This code compiles but has not been tested on hardware yet, this was largely based on a previous implementation I wrote for a different MCU
2024-04-13 temperature sensor working
2024-04-15 Communication with external ADC working
    The SPI communication with the MCP3464 IC works, but reading values has not been implemented yet
2024-04-20 MCP3464 interupt read functional
    Still needs to be tested to ensure accuracy, but the ADC read works
2024-04-23 Analog measurement demo working
    The device will connect to wifi and transmit its readings from channel one, as well as the temperature.
2024-04-24 Single Channel Demo with current stimulation
    Can now receive data over UDP and create a sine wave or square wave with arbitrary amplitude from received data.
    Matlab demo is now made using UI elements to make it possible to send commands to the device using a dropdown menu to select the wave and a slider to select the amplitude.
2024-04-24 adc broken
2024-04-25 debuging
2024-04-25 onboard ADC demo working
    current sensing not added yet
2024-04-25 current measurement working
    still using the onboard adc
2024-04-25 Formatting update
    Added comments to code
2024-04-25 add schematics
2024-04-25 change background color of schematics
    makes them readable in darkmode
2024-04-25 Rename Neural_Interface-Analog Frontend.svg to Neural_Interface-Analog_Frontend.svg
    remove space
2024-04-25 Rename Neural_Interface-Power Manegement.svg to Neural_Interface-Power_Manegement.svg
    remove space
2024-04-25 add more figures
2024-04-26 fix svg files
2024-04-26 add manufacturing files
2024-04-26 Update README.md
    fix figures
2024-04-26 update code to use MCP3464 again
2024-05-02 Remove personal logo
    The project will be made open source, but the logo will not fall under that license so I am removing it.
2024-05-02 Create LICENSE
